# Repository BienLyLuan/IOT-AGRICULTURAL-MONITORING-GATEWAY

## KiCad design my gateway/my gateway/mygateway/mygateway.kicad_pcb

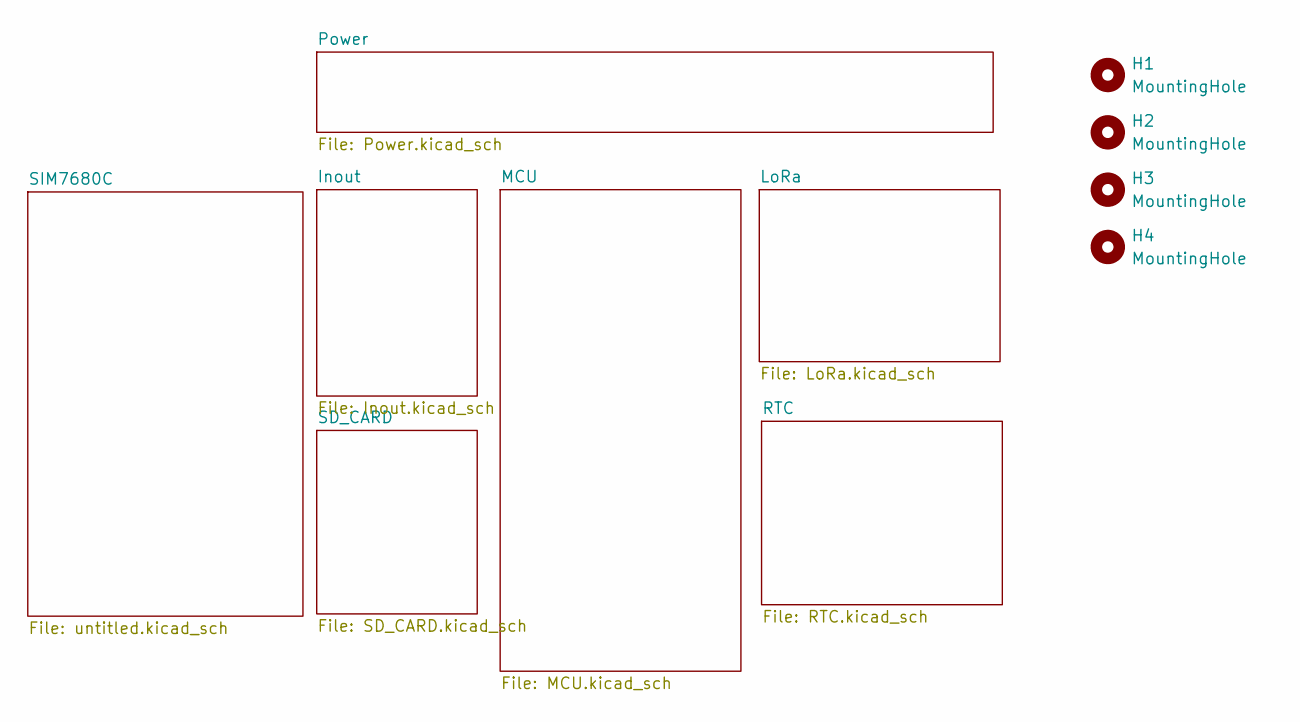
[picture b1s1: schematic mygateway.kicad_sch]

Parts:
H1, H2, H3, H4: MountingHole; MountingHole_3.2mm_M3_Pad_Via

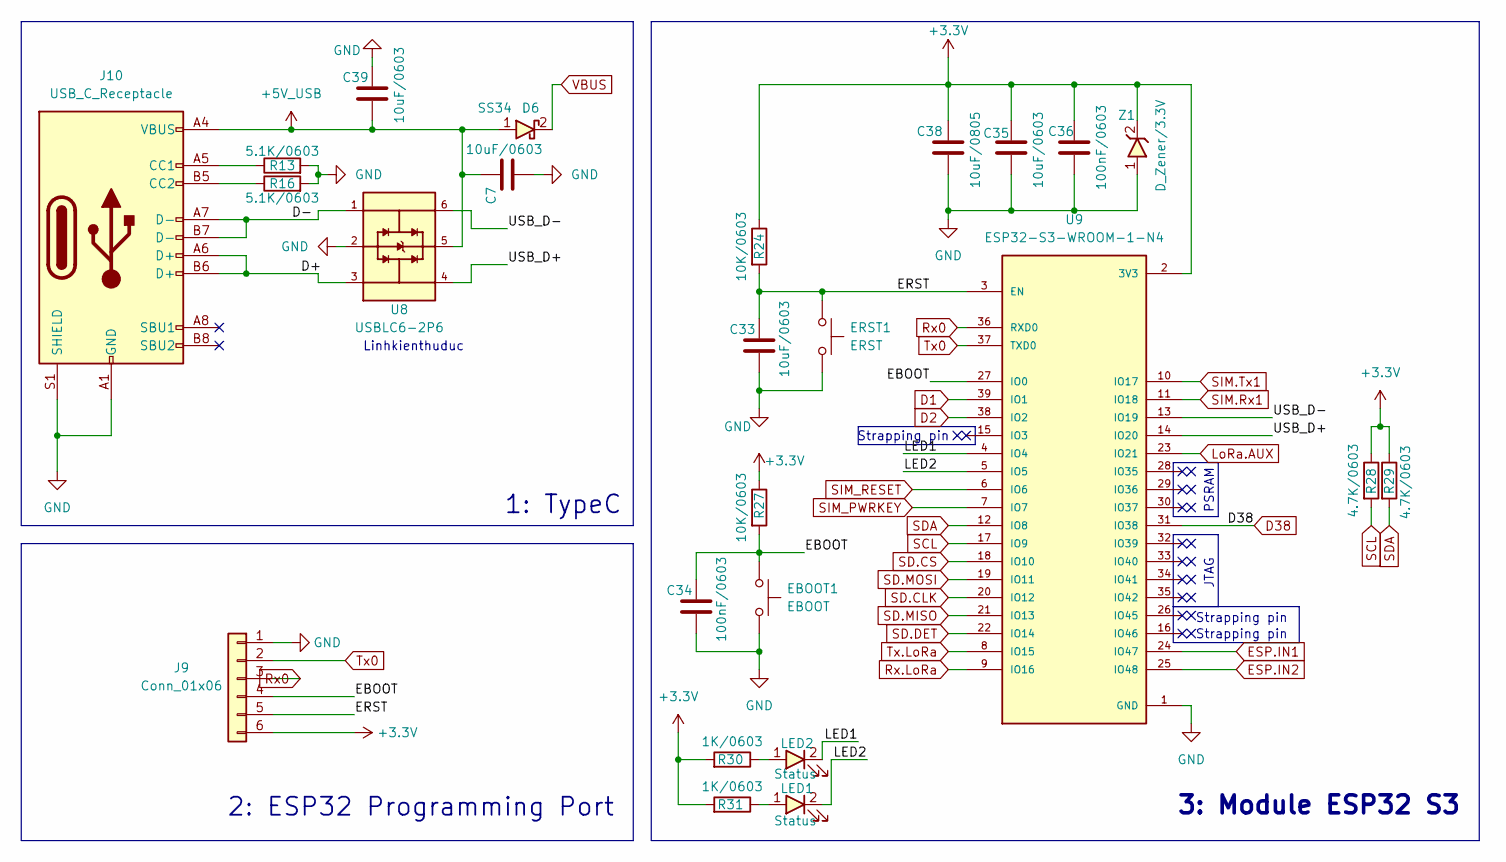
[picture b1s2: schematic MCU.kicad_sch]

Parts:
C7, C33, C35, C39: 10uF/0603; C_0603_1608Metric_Pad1.08x0.95mm_HandSolder
C34, C36: 100nF/0603; C_0603_1608Metric_Pad1.08x0.95mm_HandSolder
C38: 10uF/0805; C_0603_1608Metric_Pad1.08x0.95mm_HandSolder
D6: SS34; D_SMA
EBOOT1: EBOOT; SW_Tactile_SPST_NO_Straight_CK_PTS636Sx25SMTRLFS
ERST1: ERST; SW_Tactile_SPST_NO_Straight_CK_PTS636Sx25SMTRLFS
J9: Conn_01x06; PinHeader_1x06_P2.54mm_Vertical
J10: USB_C_Receptacle; USB_TypeC_16pin
LED1, LED2: Status; LED_0603_1608Metric_Pad1.05x0.95mm_HandSolder
R13, R16: 5.1K/0603; R_0603_1608Metric_Pad0.98x0.95mm_HandSolder
R24, R27: 10K/0603; R_0603_1608Metric_Pad0.98x0.95mm_HandSolder
R28, R29: 4.7K/0603; R_0603_1608Metric_Pad0.98x0.95mm_HandSolder
R30, R31: 1K/0603; R_0603_1608Metric_Pad0.98x0.95mm_HandSolder
U8: USBLC6-2P6; SOT-23-6; PARTREV 5
U9: ESP32-S3-WROOM-1-N4; XCVR_ESP32-S3-WROOM-1-N4; PARTREV v1.0
Z1: D_Zener/3.3V; D_SOD-123

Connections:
+3.3V: C35.1, C36.1, C38.1, J9.6, R24.1, R27.1, R28.1, R29.1, R30.2, R31.2, U9.2 (3V3), Z1.2; also elsewhere on the board
+5V_USB: C7.1, C39.2, D6.1, J10.A4 (VBUS), J10.A9 (VBUS), J10.B4 (VBUS), J10.B9 (VBUS), U8.5
/MCU/D+: J10.A6 (D+), J10.B6 (D+), U8.3
/MCU/D-: J10.A7 (D-), J10.B7 (D-), U8.1
/MCU/EBOOT: C34.1, EBOOT1.1, J9.4, R27.2, U9.27 (IO0)
/MCU/ERST: C33.1, ERST1.1, J9.5, R24.2, U9.3 (EN)
/MCU/LED1: LED2.2, U9.4 (IO4)
/MCU/LED2: LED1.2, U9.5 (IO5); also elsewhere on the board
/MCU/USB_D+: U8.4, U9.14 (IO20)
/MCU/USB_D-: U8.6, U9.13 (IO19)
D1: U9.39 (IO1); also elsewhere on the board
D2: U9.38 (IO2); also elsewhere on the board
D38: U9.31 (IO38); also elsewhere on the board
ESP.IN1: U9.24 (IO47); also elsewhere on the board
ESP.IN2: U9.25 (IO48); also elsewhere on the board
GND: C7.2, C33.2, C34.2, C35.2, C36.2, C38.2, C39.1, EBOOT1.2, ERST1.2, J9.1, J10.A1 (GND), J10.A12 (GND), J10.B1 (GND), J10.B12 (GND), J10.S1 (SHIELD), R13.2, R16.2, U8.2, U9.1 (GND), U9.40 (GND), Z1.1; also elsewhere on the board
LoRa.AUX: U9.23 (IO21); also elsewhere on the board
unnamed: J10.A5 (CC1), R13.1
unnamed: J10.B5 (CC2), R16.1
unnamed 55: LED1.1, R31.1; also elsewhere on the board
unnamed: LED2.1, R30.1
Rx0: J9.3, U9.36 (RXD0); also elsewhere on the board
Rx.LoRa: U9.9 (IO16); also elsewhere on the board
SCL: R28.2, U9.17 (IO9); also elsewhere on the board
SD.CLK: U9.20 (IO12); also elsewhere on the board
SD.CS: U9.18 (IO10); also elsewhere on the board
SD.DET: U9.22 (IO14); also elsewhere on the board
SD.MISO: U9.21 (IO13); also elsewhere on the board
SD.MOSI: U9.19 (IO11); also elsewhere on the board
SDA: R29.2, U9.12 (IO8); also elsewhere on the board
SIM.Rx1: U9.11 (IO18); also elsewhere on the board
SIM.Tx1: U9.10 (IO17); also elsewhere on the board
SIM_PWRKEY: U9.7 (IO7); also elsewhere on the board
SIM_RESET: U9.6 (IO6); also elsewhere on the board
Tx0: J9.2, U9.37 (TXD0); also elsewhere on the board
Tx.LoRa: U9.8 (IO15); also elsewhere on the board
VBUS: D6.2; also elsewhere on the board

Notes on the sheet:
2: ESP32 Programming Port
Strapping pin
PSRAM
3: Module ESP32 S3
1: TypeC
Linhkienthuduc
JTAG

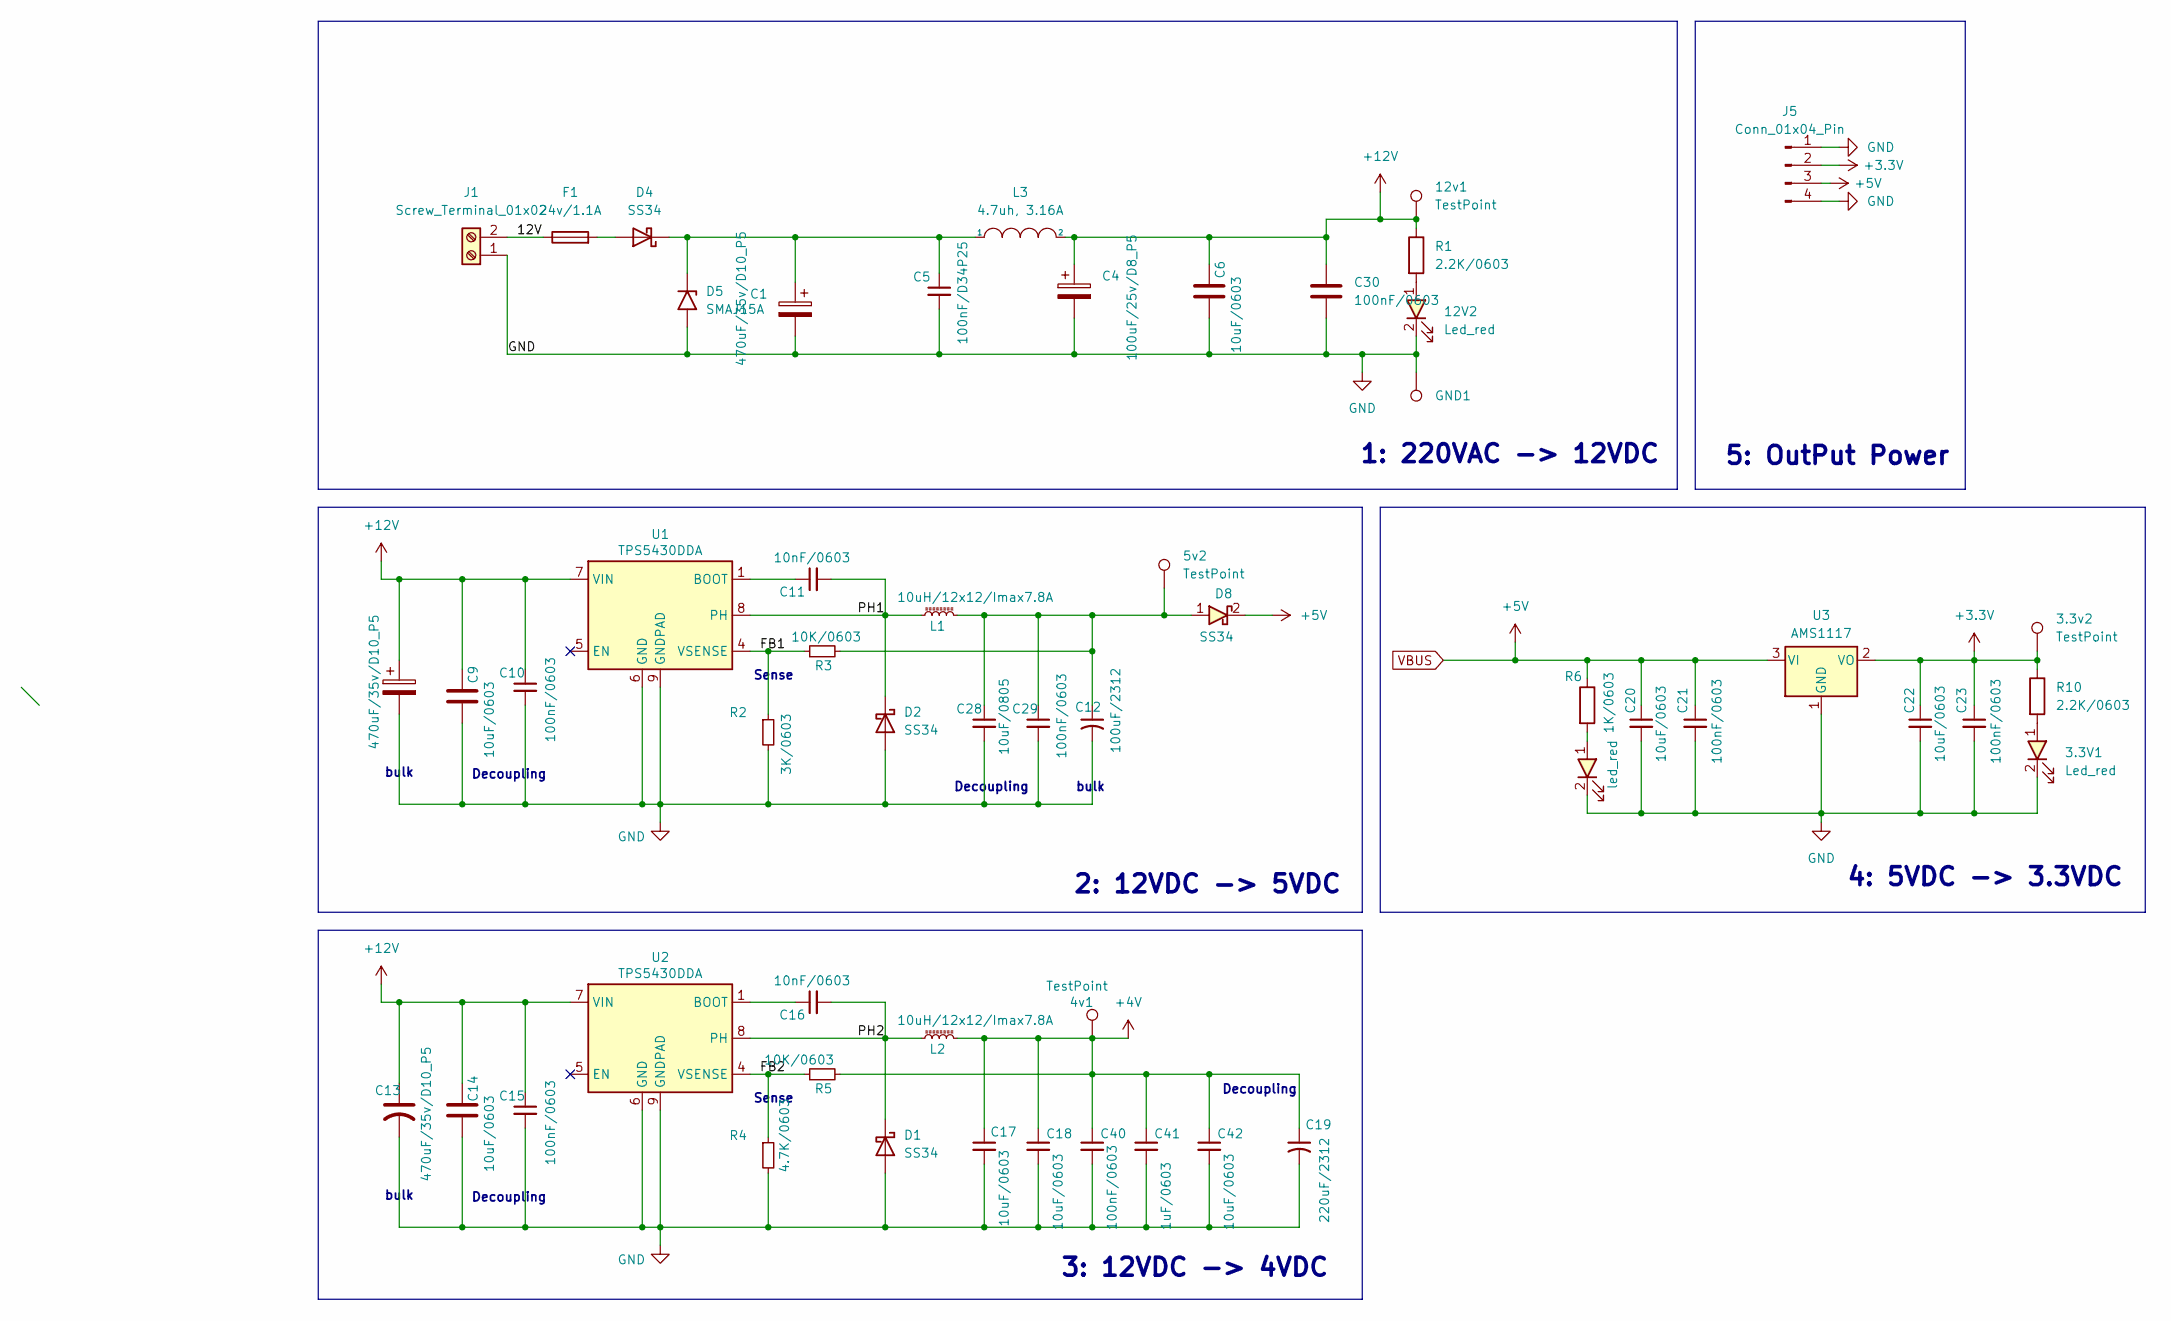
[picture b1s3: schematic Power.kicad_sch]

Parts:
3.3V1, 12V2: Led_red; LED_0603_1608Metric_Pad1.05x0.95mm_HandSolder
3.3v2, 4v1, 5v2, 12v1: TestPoint; TestPoint_Pad_1.0x1.0mm
5V1: led_red; LED_0603_1608Metric_Pad1.05x0.95mm_HandSolder; LCSC C965799
C1, C8, C13: 470uF/35v/D10_P5; CP_Radial_D10.0mm_P5.00mm
C4: 100uF/25v/D8_P5; CP_Radial_D8.0mm_P2.50mm
C5: 100nF/D34P25; C_Disc_D3.4mm_W2.1mm_P2.50mm; LCSC C1945
C6, C9, C14: 10uF/0603; C_0603_1608Metric_Pad1.08x0.95mm_HandSolder
C10, C15: 100nF/0603; C_1206_3216Metric_Pad1.33x1.80mm_HandSolder; LCSC C1945
C11, C16: 10nF/0603; C_0603_1608Metric_Pad1.08x0.95mm_HandSolder; LCSC C1589
C12: 100uF/2312; CP_EIA-6032-15_Kemet-U_Pad2.25x2.35mm_HandSolder
C17, C18, C42: 10uF/0603; C_0805_2012Metric_Pad1.18x1.45mm_HandSolder; LCSC C1849
C19: 220uF/2312; CP_EIA-6032-15_Kemet-U_Pad2.25x2.35mm_HandSolder
C20, C22: 10uF/0603; C_0603_1608Metric_Pad1.08x0.95mm_HandSolder; LCSC C1945
C21, C23: 100nF/0603; C_0603_1608Metric_Pad1.08x0.95mm_HandSolder; LCSC C1849
C28: 10uF/0805; C_0805_2012Metric_Pad1.18x1.45mm_HandSolder; LCSC C13585
C29: 100nF/0603; C_0603_1608Metric_Pad1.08x0.95mm_HandSolder; LCSC C1945
C30: 100nF/0603; C_0603_1608Metric_Pad1.08x0.95mm_HandSolder
C40: 100nF/0603; C_0805_2012Metric_Pad1.18x1.45mm_HandSolder; LCSC C1849
C41: 1uF/0603; C_0805_2012Metric_Pad1.18x1.45mm_HandSolder; LCSC C1849
D1, D2, D4, D8: SS34; D_SMA
D5: SMAJ15A; D_SMA
F1: 24v/1.1A; Fuse_1812_4532Metric_Pad1.30x3.40mm_HandSolder
GND1: TestPoint; TestPoint_Pad_1.0x1.0mm
J1: Screw_Terminal_01x02; TerminalBlock_bornier-2_P5.08mm
J5: Conn_01x04_Pin; PinHeader_1x04_P2.54mm_Vertical
L1, L2: 10uH/12x12/Imax7.8A; L_Bourns_SRR1208_12.7x12.7mm; LCSC C2929499
L3: 4.7uh, 3.16A; L_Wuerth_WE-PD-Typ-7345
R1, R10: 2.2K/0603; R_0603_1608Metric_Pad0.98x0.95mm_HandSolder
R2: 3K/0603; R_0603_1608Metric_Pad0.98x0.95mm_HandSolder; LCSC C22978
R3, R5: 10K/0603; R_0603_1608Metric_Pad0.98x0.95mm_HandSolder; LCSC C25804
R4: 4.7K/0603; R_0603_1608Metric_Pad0.98x0.95mm_HandSolder; LCSC C22978
R6: 1K/0603; R_0603_1608Metric_Pad0.98x0.95mm_HandSolder; LCSC C14676
U1, U2: TPS5430DDA; VREG_LM5017MR_NOPB; LCSC C9864
U3: AMS1117; SOT-223-3_TabPin2

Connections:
+3.3V: 3.3v2.1, C22.1, C23.1, J5.2, R10.1, U3.2 (VO); also elsewhere on the board
+4V: 4v1.1, C17.1, C18.1, C19.1, C40.1, C41.1, C42.1, L2.2, R5.2; also elsewhere on the board
+12V: 12v1.1, C4.1, C6.1, C8.1, C9.1, C10.1, C13.1, C14.1, C15.1, C30.1, L3.2, R1.1, U1.7 (VIN), U2.7 (VIN); also elsewhere on the board
/Power/12V: F1.1, J1.2
/Power/FB1: R2.1, R3.1, U1.4 (VSENSE)
/Power/FB2: R4.1, R5.1, U2.4 (VSENSE)
/Power/PH1: C11.2, D2.1 (K), L1.1, U1.8 (PH)
/Power/PH2: C16.2, D1.1 (K), L2.1, U2.8 (PH)
GND: 3.3V1.2, 5V1.2, 12V2.2, C1.2, C4.2, C5.2, C6.2, C8.2, C9.2, C10.2, C12.2, C13.2, C14.2, C15.2, C17.2, C18.2, C19.2, C20.2, C21.2, C22.2, C23.2, C28.2, C29.2, C30.2, C40.2, C41.2, C42.2, D1.2 (A), D2.2 (A), D5.2 (A2), GND1.1, J1.1, J5.1, J5.4, R2.2, R4.2, U1.6 (GND), U1.9 (GNDPAD), U2.6 (GND), U2.9 (GNDPAD), U3.1 (GND); also elsewhere on the board
unnamed 37: 3.3V1.1, R10.2; also elsewhere on the board
unnamed 38: 5V1.1, R6.2; also elsewhere on the board
unnamed 39: 5v2.1, C12.1, C28.1, C29.1, D8.1, L1.2, R3.2; also elsewhere on the board
unnamed 40: 12V2.1, R1.2; also elsewhere on the board
unnamed: D4.2 (A), F1.2
unnamed: C1.1, C5.1, D4.1 (K), D5.1 (A1), L3.1
unnamed: C11.1, U1.1 (BOOT)
unnamed: C16.1, U2.1 (BOOT)
VBUS: C20.1, C21.1, D8.2, J5.3, R6.1, U3.3 (VI); also elsewhere on the board

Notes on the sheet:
Decoupling
3: 12VDC -> 4VDC
4: 5VDC -> 3.3VDC
1: 220VAC -> 12VDC
bulk
Sense
5: OutPut Power
2: 12VDC -> 5VDC

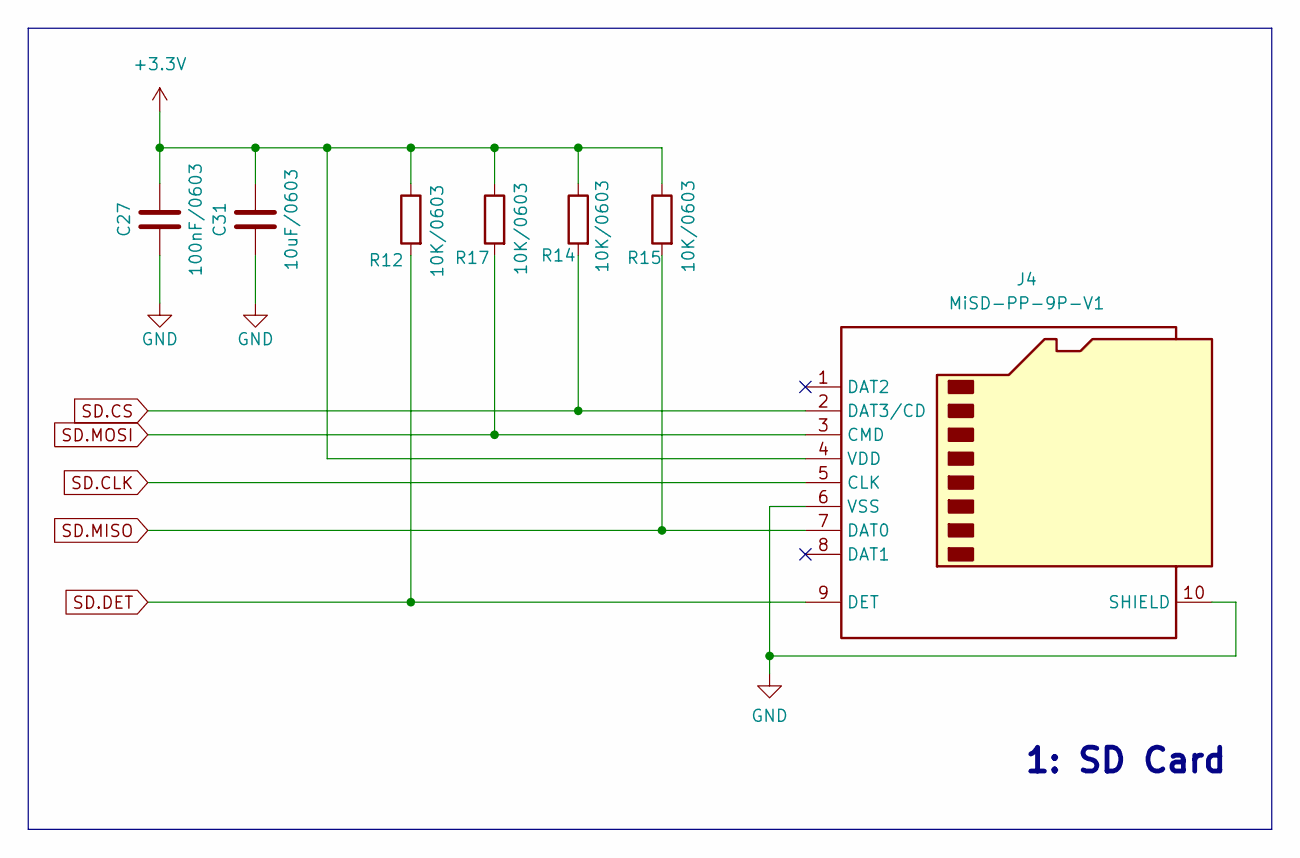
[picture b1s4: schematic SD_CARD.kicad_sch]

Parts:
C27: 100nF/0603; C_0603_1608Metric_Pad1.08x0.95mm_HandSolder
C31: 10uF/0603; C_0603_1608Metric_Pad1.08x0.95mm_HandSolder
J4: MiSD-PP-9P-V1; MicroSD_Socket_9P
R12, R14, R15, R17: 10K/0603; R_0603_1608Metric_Pad0.98x0.95mm_HandSolder

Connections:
+3.3V: C27.2, C31.2, J4.4 (VDD), R12.1, R14.1, R15.1, R17.1; also elsewhere on the board
GND: C27.1, C31.1, J4.6 (VSS), J4.10 (SHIELD); also elsewhere on the board
SD.CLK: J4.5 (CLK); also elsewhere on the board
SD.CS: J4.2 (DAT3/CD), R14.2; also elsewhere on the board
SD.DET: J4.9 (DET), R12.2; also elsewhere on the board
SD.MISO: J4.7 (DAT0), R15.2; also elsewhere on the board
SD.MOSI: J4.3 (CMD), R17.2; also elsewhere on the board

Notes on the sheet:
1: SD Card

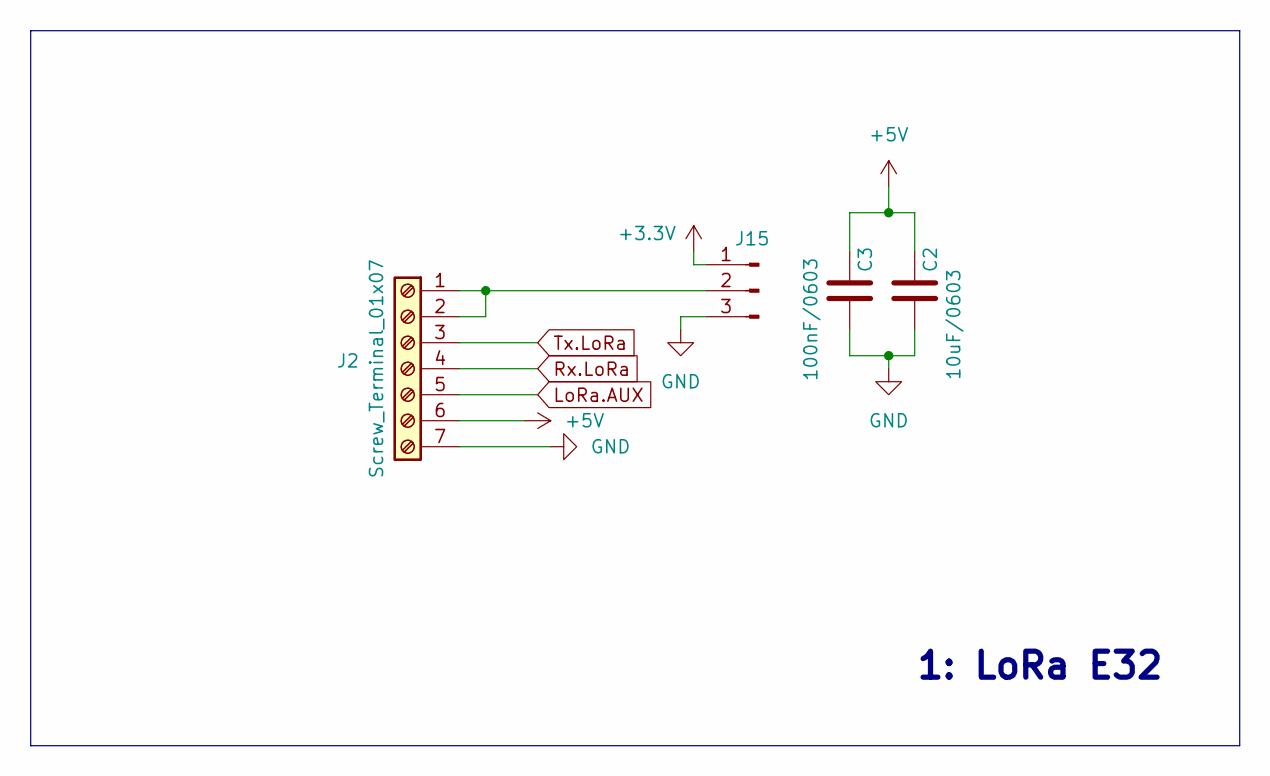
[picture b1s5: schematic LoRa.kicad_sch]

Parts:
C2: 10uF/0603; C_0603_1608Metric_Pad1.08x0.95mm_HandSolder
C3: 100nF/0603; C_0603_1608Metric_Pad1.08x0.95mm_HandSolder
J2: Screw_Terminal_01x07; lora_module
J15: Conn_01x03_Pin; PinHeader_1x03_P2.54mm_Vertical

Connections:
+3.3V: J15.1; also elsewhere on the board
GND: C2.2, C3.2, J2.7, J15.3; also elsewhere on the board
LoRa.AUX: J2.5; also elsewhere on the board
unnamed: J2.1, J2.2, J15.2
Rx.LoRa: J2.4; also elsewhere on the board
Tx.LoRa: J2.3; also elsewhere on the board
VBUS: C2.1, C3.1, J2.6; also elsewhere on the board

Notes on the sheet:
1: LoRa E32

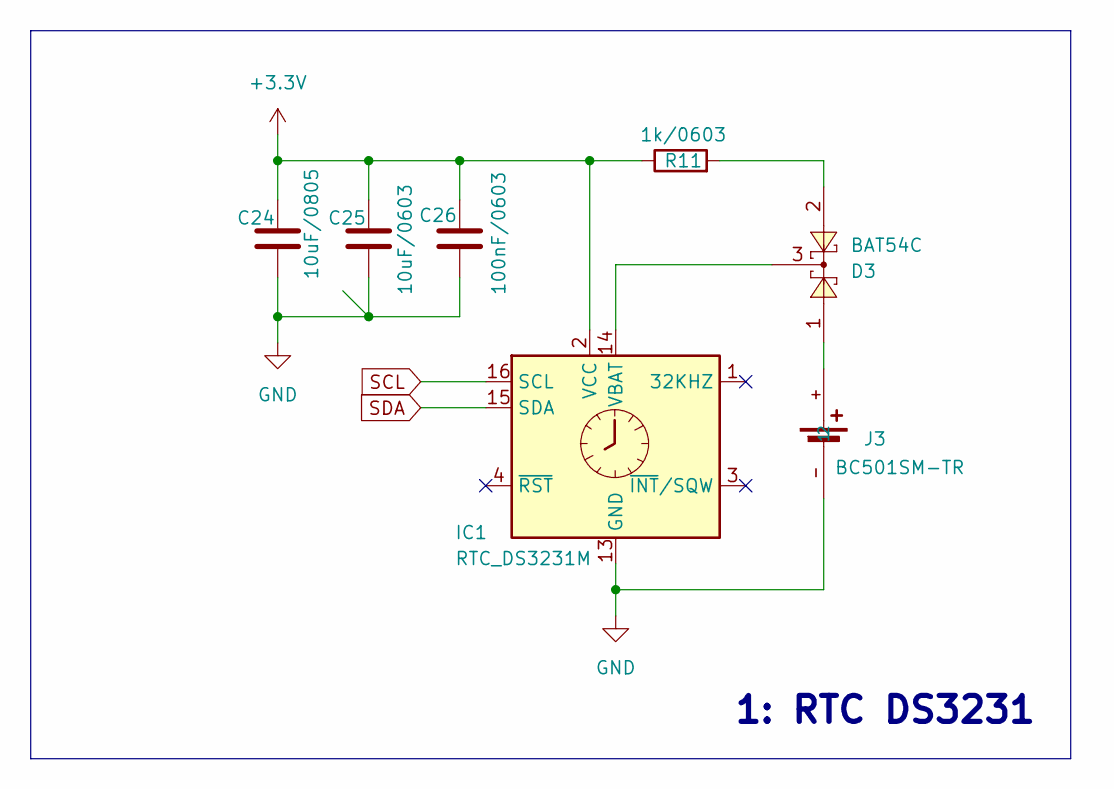
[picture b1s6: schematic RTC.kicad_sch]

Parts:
C24: 10uF/0805; C_0805_2012Metric_Pad1.18x1.45mm_HandSolder
C25: 10uF/0603; C_0603_1608Metric_Pad1.08x0.95mm_HandSolder
C26: 100nF/0603; C_0603_1608Metric_Pad1.08x0.95mm_HandSolder
D3: BAT54C; SOT23-3
IC1: RTC_DS3231M; SOIC-16W_7.5x10.3mm_P1.27mm
J3: BC501SM-TR; MPD_BC501SM-TR; MPN BC501SM-TR
R11: 1k/0603; R_0603_1608Metric_Pad0.98x0.95mm_HandSolder

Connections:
+3.3V: C24.1, C25.1, C26.1, IC1.2 (VCC), R11.1; also elsewhere on the board
GND: C24.2, C25.2, C26.2, IC1.5 (GND), IC1.6 (GND), IC1.7 (GND), IC1.8 (GND), IC1.9 (GND), IC1.10 (GND), IC1.11 (GND), IC1.12 (GND), IC1.13 (GND), J3.- (2); also elsewhere on the board
unnamed: D3.2, R11.2
unnamed: D3.3, IC1.14 (VBAT)
unnamed: D3.1, J3.+ (1)
SCL: IC1.16 (SCL); also elsewhere on the board
SDA: IC1.15 (SDA); also elsewhere on the board

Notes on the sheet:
1: RTC DS3231

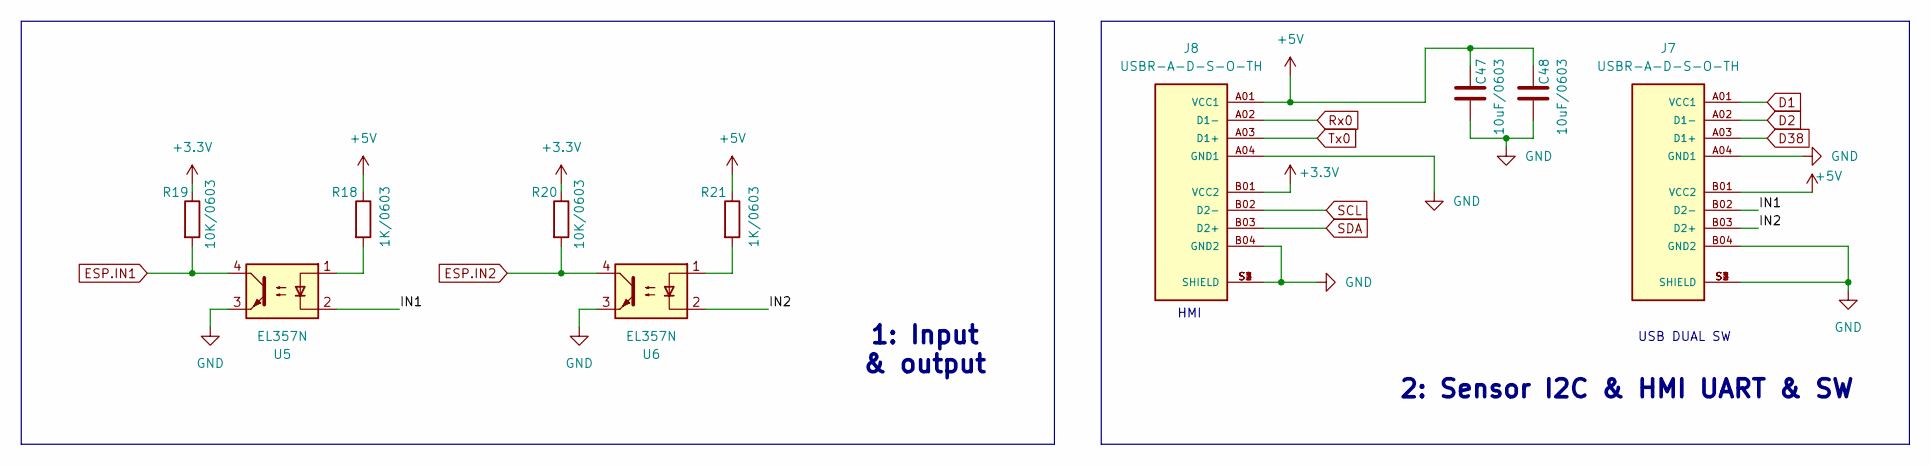
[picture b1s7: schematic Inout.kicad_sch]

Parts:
C47, C48: 10uF/0603; C_0603_1608Metric_Pad1.08x0.95mm_HandSolder
J7, J8: USBR-A-D-S-O-TH; USB2TANG
R18, R21: 1K/0603; R_0603_1608Metric_Pad0.98x0.95mm_HandSolder
R19, R20: 10K/0603; R_0603_1608Metric_Pad0.98x0.95mm_HandSolder
U5, U6: EL357N; OPTO_EL357N-G

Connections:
+3.3V: J8.B01 (VCC2), R19.1, R20.1; also elsewhere on the board
/Inout/IN1: J7.B02 (D2-), U5.2
/Inout/IN2: J7.B03 (D2+), U6.2
D1: J7.A01 (VCC1); also elsewhere on the board
D2: J7.A02 (D1-); also elsewhere on the board
D38: J7.A03 (D1+); also elsewhere on the board
ESP.IN1: R19.2, U5.4; also elsewhere on the board
ESP.IN2: R20.2, U6.4; also elsewhere on the board
GND: C47.2, C48.2, J7.A04 (GND1), J7.B04 (GND2), J7.S1 (SHIELD), J7.S2 (SHIELD), J7.S3 (SHIELD), J7.S4 (SHIELD), J8.A04 (GND1), J8.B04 (GND2), J8.S1 (SHIELD), J8.S2 (SHIELD), J8.S3 (SHIELD), J8.S4 (SHIELD), U5.3, U6.3; also elsewhere on the board
unnamed: R18.2, U5.1
unnamed: R21.2, U6.1
Rx0: J8.A02 (D1-); also elsewhere on the board
SCL: J8.B02 (D2-); also elsewhere on the board
SDA: J8.B03 (D2+); also elsewhere on the board
Tx0: J8.A03 (D1+); also elsewhere on the board
VBUS: C47.1, C48.1, J7.B01 (VCC2), J8.A01 (VCC1), R18.1, R21.1; also elsewhere on the board

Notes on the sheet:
1: Input & output
USB DUAL SW
HMI
2: Sensor I2C & HMI UART & SW

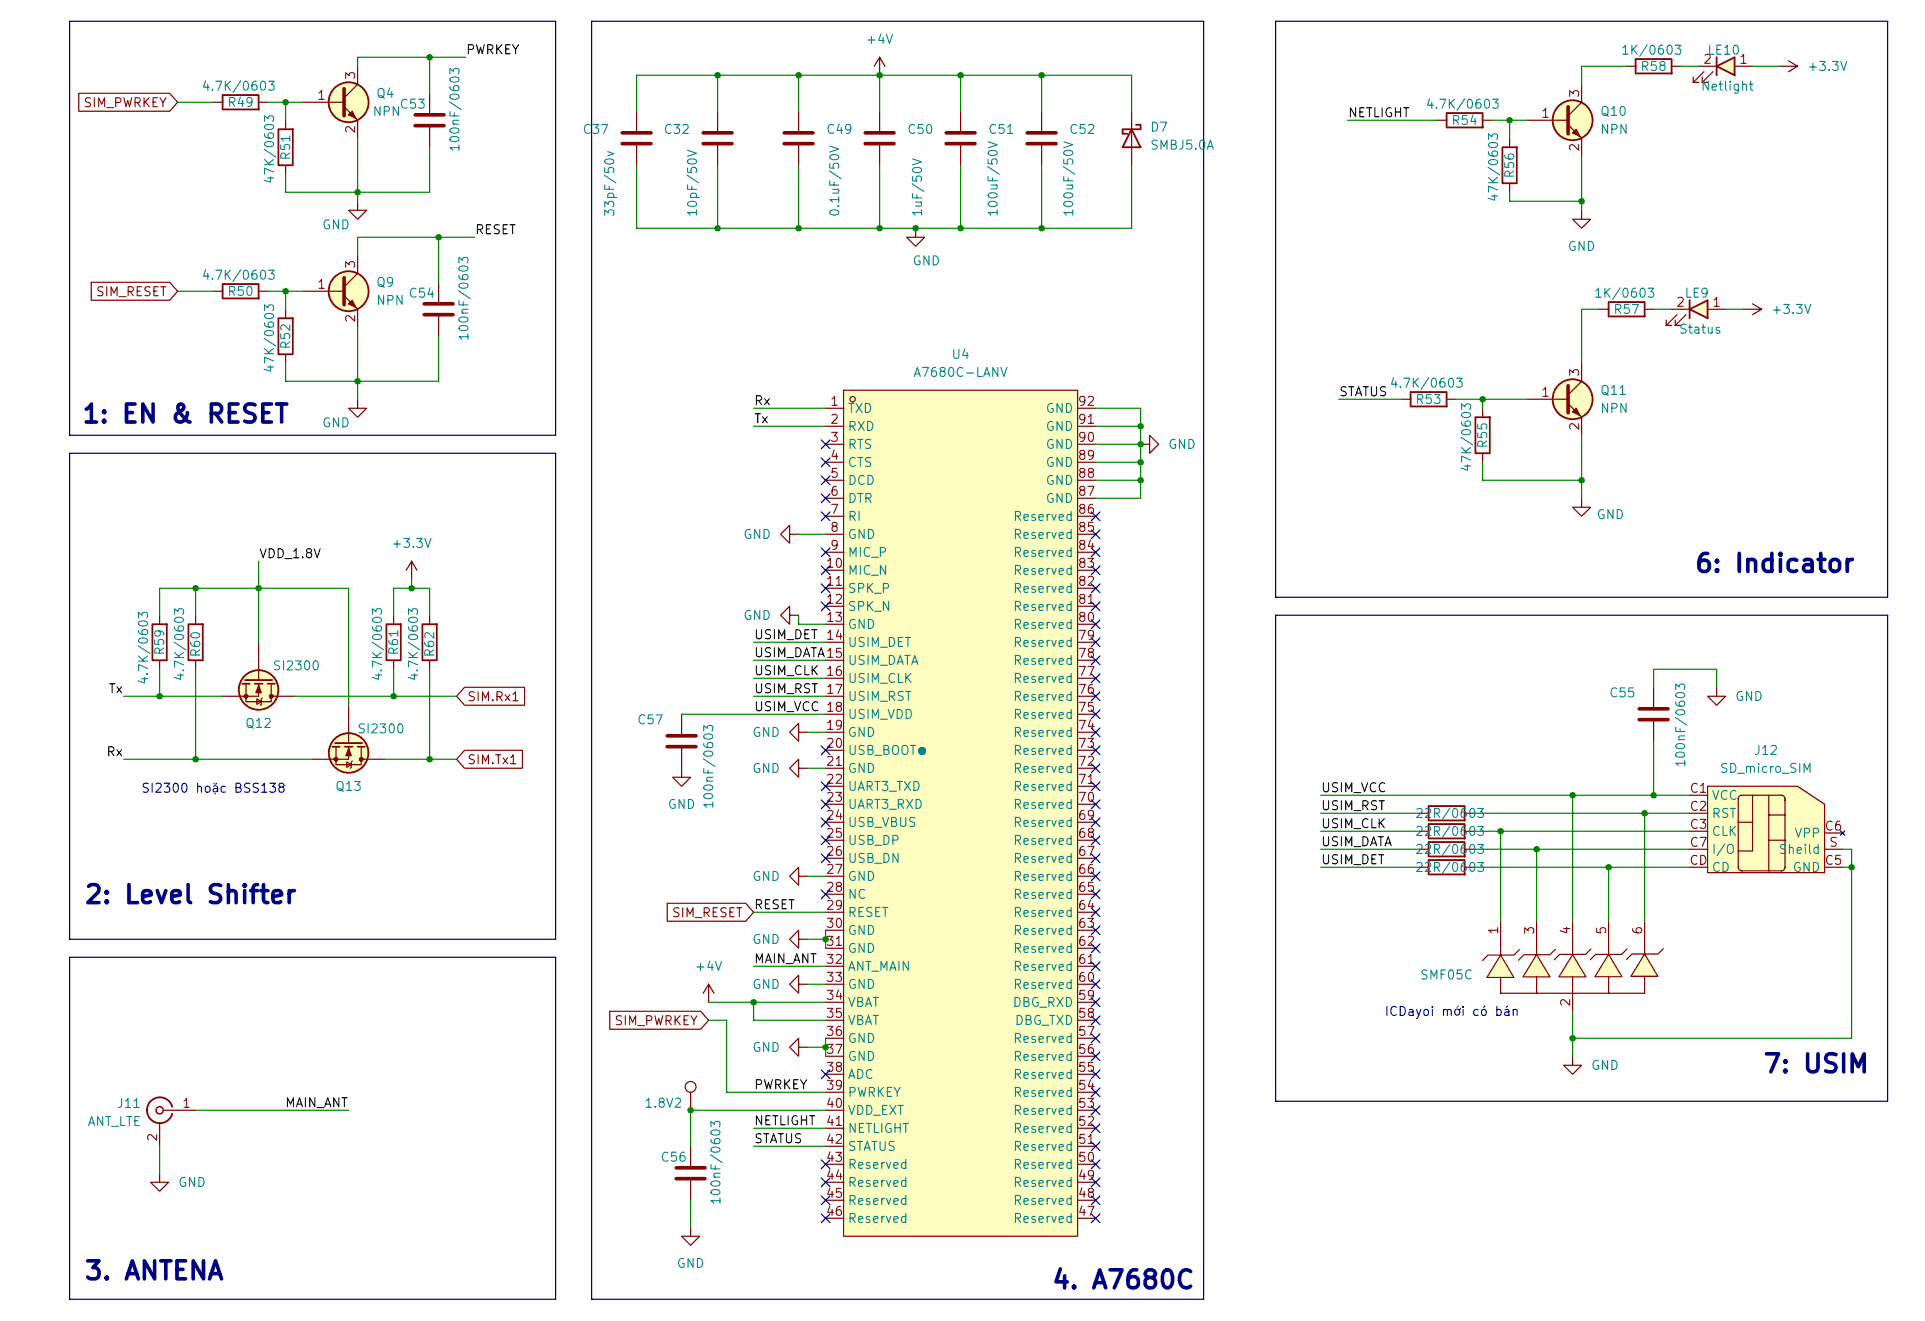
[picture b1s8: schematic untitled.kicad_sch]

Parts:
1.8V2: TestPoint; TestPoint_Pad_1.0x1.0mm
C32: 10pF/50V; C_0603_1608Metric
C37: 33pF/50v; C_0603_1608Metric
C49: 0.1uF/50V; C_0805_2012Metric
C50: 1uF/50V; C_0805_2012Metric
C51, C52: 100uF/50V; C_0805_2012Metric
C53, C54, C55, C56, C57: 100nF/0603; C_0603_1608Metric_Pad1.08x0.95mm_HandSolder
D7: SMBJ5.0A; D_SMA
D9: SMF05C; SOT-363_SC-70-6_Handsoldering
J11: ANT_LTE; U.FL_Hirose_U.FL-R-SMT-1_Vertical; MPN BWU.FL-IPEX1; LCSC C5137195
J12: SD_micro_SIM; SIMCARD
LE9: Status; LED_0603_1608Metric_Pad1.05x0.95mm_HandSolder
LE10: Netlight; LED_0603_1608Metric_Pad1.05x0.95mm_HandSolder
Q4, Q9, Q10, Q11: NPN; SOT23-3
Q12, Q13: SI2300; SOT23-3
R8, R63, R64, R65: 22R/0603; R_0603_1608Metric_Pad0.98x0.95mm_HandSolder
R49, R50, R53, R54, R59, R60, R61, R62: 4.7K/0603; R_0603_1608Metric_Pad0.98x0.95mm_HandSolder
R51, R52, R55, R56: 47K/0603; R_0603_1608Metric_Pad0.98x0.95mm_HandSolder
R57, R58: 1K/0603; R_0603_1608Metric_Pad0.98x0.95mm_HandSolder
U4: A7680C-LANV; LCC-LAG_L17.6-W15.7_A7680C; MPN A7680C-LANV; LCSC Part C5381968

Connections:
+3.3V: LE9.1, LE10.1, R61.2, R62.2; also elsewhere on the board
+4V: C32.1, C37.1, C49.1, C50.1, C51.1, C52.1, D7.1 (K), U4.34 (VBAT), U4.35 (VBAT); also elsewhere on the board
/SIM7680C/MAIN_ANT: J11.1 (In), U4.32 (ANT_MAIN)
/SIM7680C/NETLIGHT: R54.1, U4.41 (NETLIGHT)
/SIM7680C/Rx: Q13.2 (S), R60.1, U4.1 (TXD)
/SIM7680C/STATUS: R53.1, U4.42 (STATUS)
/SIM7680C/Tx: Q12.2 (S), R59.1, U4.2 (RXD)
/SIM7680C/USIM_CLK: R64.1, U4.16 (USIM_CLK)
/SIM7680C/USIM_DATA: R65.1, U4.15 (USIM_DATA)
/SIM7680C/USIM_DET: R8.1, U4.14 (USIM_DET)
/SIM7680C/USIM_RST: R63.1, U4.17 (USIM_RST)
/SIM7680C/USIM_VCC: C55.2, C57.1, D9.4, J12.C1 (VCC), U4.18 (USIM_VDD)
/SIM7680C/VDD_1.8V: Q12.1 (G), Q13.1 (G), R59.2, R60.2
GND: C32.2, C37.2, C49.2, C50.2, C51.2, C52.2, C53.2, C54.2, C55.1, C56.2, C57.2, D7.2 (A), D9.2, J11.2 (Ext), J12.C5 (GND), J12.S (Sheild), Q4.2 (E), Q9.2 (E), Q10.2 (E), Q11.2 (E), R51.1, R52.1, R55.1, R56.1, U4.8 (GND), U4.13 (GND), U4.19 (GND), U4.21 (GND), U4.27 (GND), U4.30 (GND), U4.31 (GND), U4.33 (GND), U4.36 (GND), U4.37 (GND), U4.87 (GND), U4.88 (GND), U4.89 (GND), U4.90 (GND), U4.91 (GND), U4.92 (GND); also elsewhere on the board
unnamed: D9.5, J12.CD, R8.2
unnamed: D9.1, J12.C3 (CLK), R64.2
unnamed: D9.3, J12.C7 (I/O), R65.2
unnamed: D9.6, J12.C2 (RST), R63.2
unnamed 53: LE9.2, R57.2; also elsewhere on the board
unnamed 54: LE10.2, R58.2; also elsewhere on the board
unnamed: Q4.1 (B), R49.2, R51.2
unnamed: Q9.1 (B), R50.2, R52.2
unnamed: Q10.1 (B), R54.2, R56.2
unnamed: Q10.3 (C), R58.1
unnamed: Q11.1 (B), R53.2, R55.2
unnamed: Q11.3 (C), R57.1
unnamed 67: 1.8V2.1, C56.1, U4.40 (VDD_EXT); also elsewhere on the board
SIM.Rx1: Q12.3 (D), R61.1; also elsewhere on the board
SIM.Tx1: Q13.3 (D), R62.1; also elsewhere on the board
SIM_PWRKEY: C53.1, Q4.3 (C), R49.1, U4.39 (PWRKEY); also elsewhere on the board
SIM_RESET: C54.1, Q9.3 (C), R50.1, U4.29 (RESET); also elsewhere on the board

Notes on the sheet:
4. A7680C
3. ANTENA
7: USIM
2: Level Shifter
6: Indicator
1: EN & RESET
ICDayoi mới có bán
SI2300 hoặc BSS138

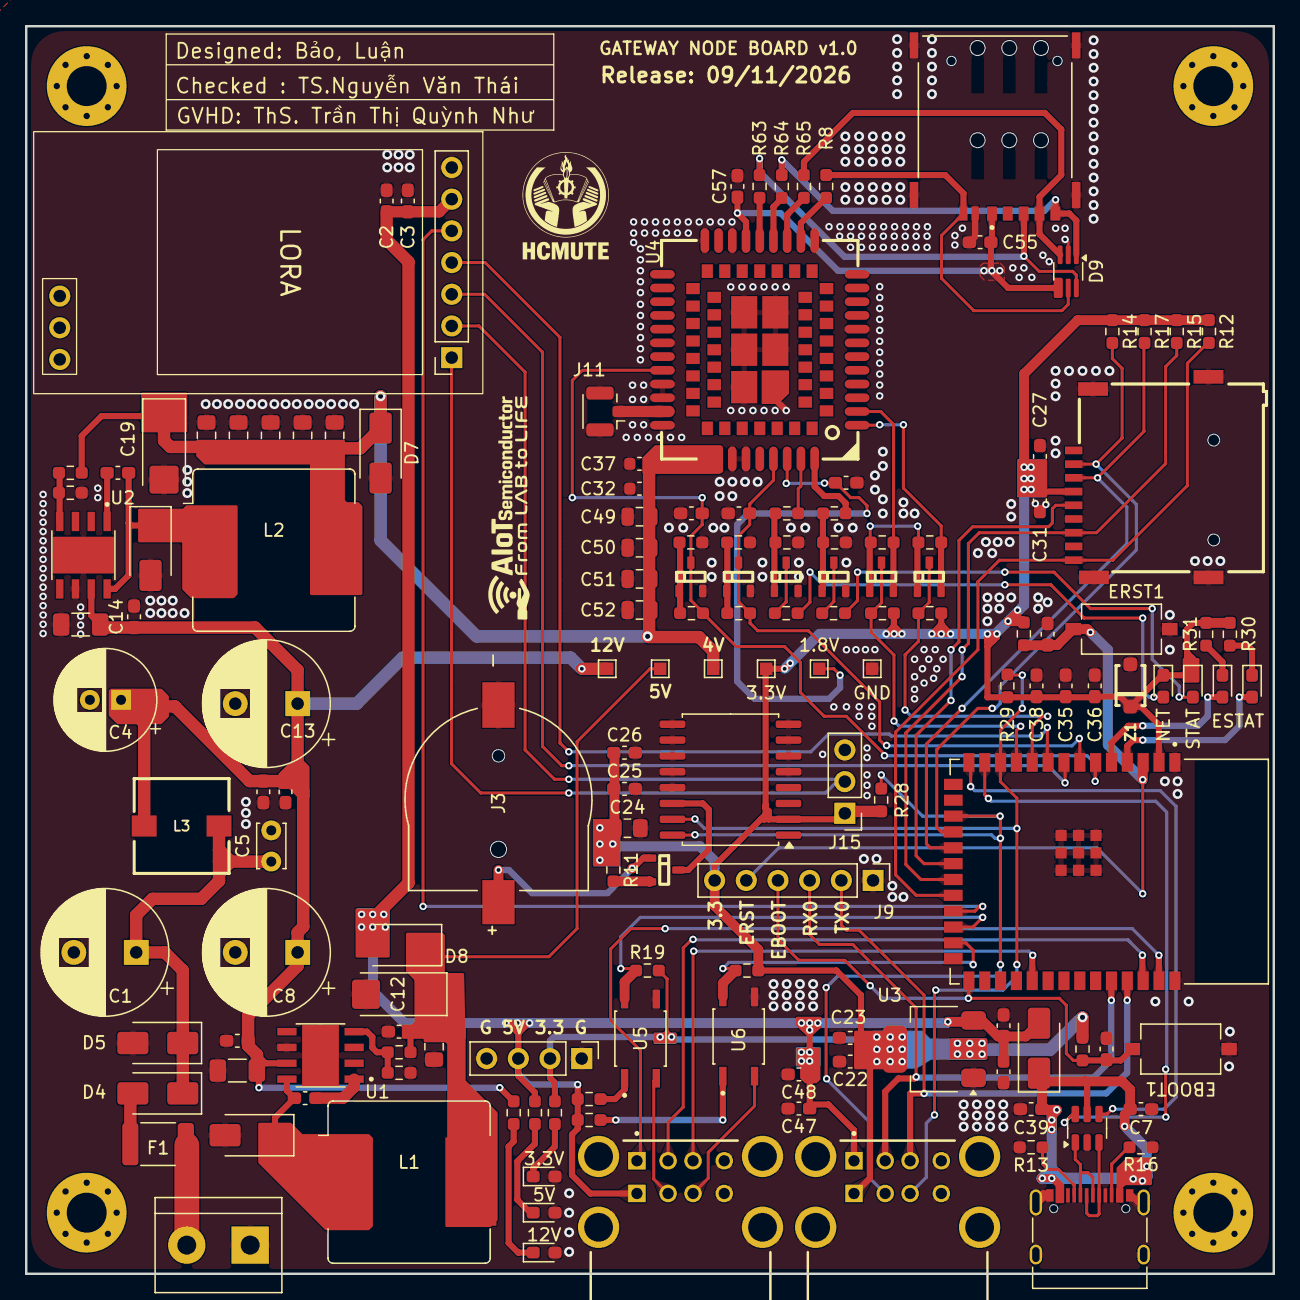
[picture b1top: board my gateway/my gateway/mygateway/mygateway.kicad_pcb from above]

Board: 2 copper layers, 100.0 x 100.0 mm, 156 parts (0 on the bottom side), 84 nets.

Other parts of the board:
1.8V, 3.3V#2, 4V, 5V#2, 12V: TestPoint; TestPoint_Pad_1.0x1.0mm
3.3V, 12V#2: Led_red; LED_0603_1608Metric_Pad1.05x0.95mm_HandSolder
5V: led_red; LED_0603_1608Metric_Pad1.05x0.95mm_HandSolder
ESTAT: Status; LED_0603_1608Metric_Pad1.05x0.95mm_HandSolder
GND: TestPoint; TestPoint_Pad_1.0x1.0mm
NET: Netlight; LED_0603_1608Metric_Pad1.05x0.95mm_HandSolder
Ref**: LOGO; hcmute
STAT: Status; LED_0603_1608Metric_Pad1.05x0.95mm_HandSolder

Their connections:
+3.3V: 3.3V#2.1 (1_1), NET.1, STAT.1; also elsewhere on the board
+4V: 4V.1 (1_1); also elsewhere on the board
+12V: 12V.1 (1_1); also elsewhere on the board
/MCU/LED2: ESTAT.2; also elsewhere on the board
GND: 3.3V.2, 5V.2, 12V#2.2, GND.1 (1_1); also elsewhere on the board
unnamed 37: 3.3V.1; also elsewhere on the board
unnamed 38: 5V.1; also elsewhere on the board
unnamed 39: 5V#2.1 (1_1); also elsewhere on the board
unnamed 40: 12V#2.1; also elsewhere on the board
unnamed 53: STAT.2; also elsewhere on the board
unnamed 54: NET.2; also elsewhere on the board
unnamed 55: ESTAT.1; also elsewhere on the board
unnamed 67: 1.8V.1 (1_1); also elsewhere on the board
